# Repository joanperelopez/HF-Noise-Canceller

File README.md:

# HF Noise Canceller for ham radio

This project was born out of necessity for my day-to-day activities as a ham radio operator. The QRM is becoming more intense every day, with current levels reaching S9, so I needed to find a way to reduce it.  

All the noise cancellers I know are based on the same principle: the use of an auxiliary antenna that picks up the noise, which is then phase-inverted, amplified, and mixed with the signal-plus-noise coming from the main antenna. By properly adjusting the amplitude and phase in the noise amplifier, part of that noise can be canceled out.

#### Note: This device is still in the design phase and the circuit has not yet been tested.

The original design is based on an article for building a noise canceller by colleague EA1KO, which in turn is very similar to a commercial one. I have applied some modifications that presumably could improve its performance, such as:

1. The incorporation of signal relays instead of extending the RF cables to the switches. This ensures that the wiring is entirely DC, with no RF signals. Due to these relays, the wiring is simplified.

2. The addition of a 1.2 MHz high-pass filter at the input of the auxiliary antenna. The use of this filter can be selected or bypassed via a switch.

3. PTT input from the transceiver to switch the canceller to transmit mode (in this mode, the power relay creates a bypass between the main antenna and the transceiver). The automatic switching when RF is detected is only as a safety measure.

4. LA1, LA2, and LA3 are 12V bulbs used to protect sensitive circuits from RF power when the equipment is in transmission mode.

5. The addition of shielding in the first stage of noise amplification, to prevent noise that does not come from the auxiliary antenna.

6. A careful design of the ground connections, their points of connection to the main ground, and the power supply inputs.

7. Adjustment of the delay time from when the PTT is released until the device returns to reception mode.

8. A single power relay for antenna switching.

_Top view of the 3D model._

_Bottom view of the 3D model._

### Additional information for assembly:  

1. Once the SMD and THT components are mounted on the PCB, the jumpers marked from JP1 to JP6 need to be short-circuited. These jumpers are a very effective method to determine where the ground connections and power supply positives are linked across the entire PCB.

2. A 50-ohm coaxial cable needs to be placed to connect TP15 and TP13 with TP14 and TP12, respectively. I have preferred this connection to be made using an external cable rather than a copper trace to avoid possible interference (EMI). This cable is marked in the PCB silkscreen.

3. All cables going to connectors and switches must be connected to the corresponding TPn, according to the schematic.

_PCB Top side._

_PCB Bottom side._

### RF Transformers
All the transformers used in the design are identical. The ferrite cores employed are BN-73-302 or similar, with a permeability of around 2500.

To make each transformer, two wires of different colors (to easily identify their ends) need to be twisted together. With this twisted wire, five turns must be wound around the toroid, keeping in mind that each time the wire passes through a hole in the toroid, it counts as one turn. 

The figure shows how to number the terminals to correctly install the transformers on the printed circuit board.

_Detail of each transformer and their terminal numbers._

_3D model top view._

_3D model front view. You must include knobs to adjust the potentiometers._

_3D model rear view._

_Printed 3D prototype. Ready to be used._ 

_Printed 3D prototype. Ready to be used._ 

_Printed 3D potentiometer extender. Ready to be used._ 

### Errors found
1. Q2 and Q5 have the E and the B footprints interchanged.
2. The diodes 1N4148 have the footprint to small.

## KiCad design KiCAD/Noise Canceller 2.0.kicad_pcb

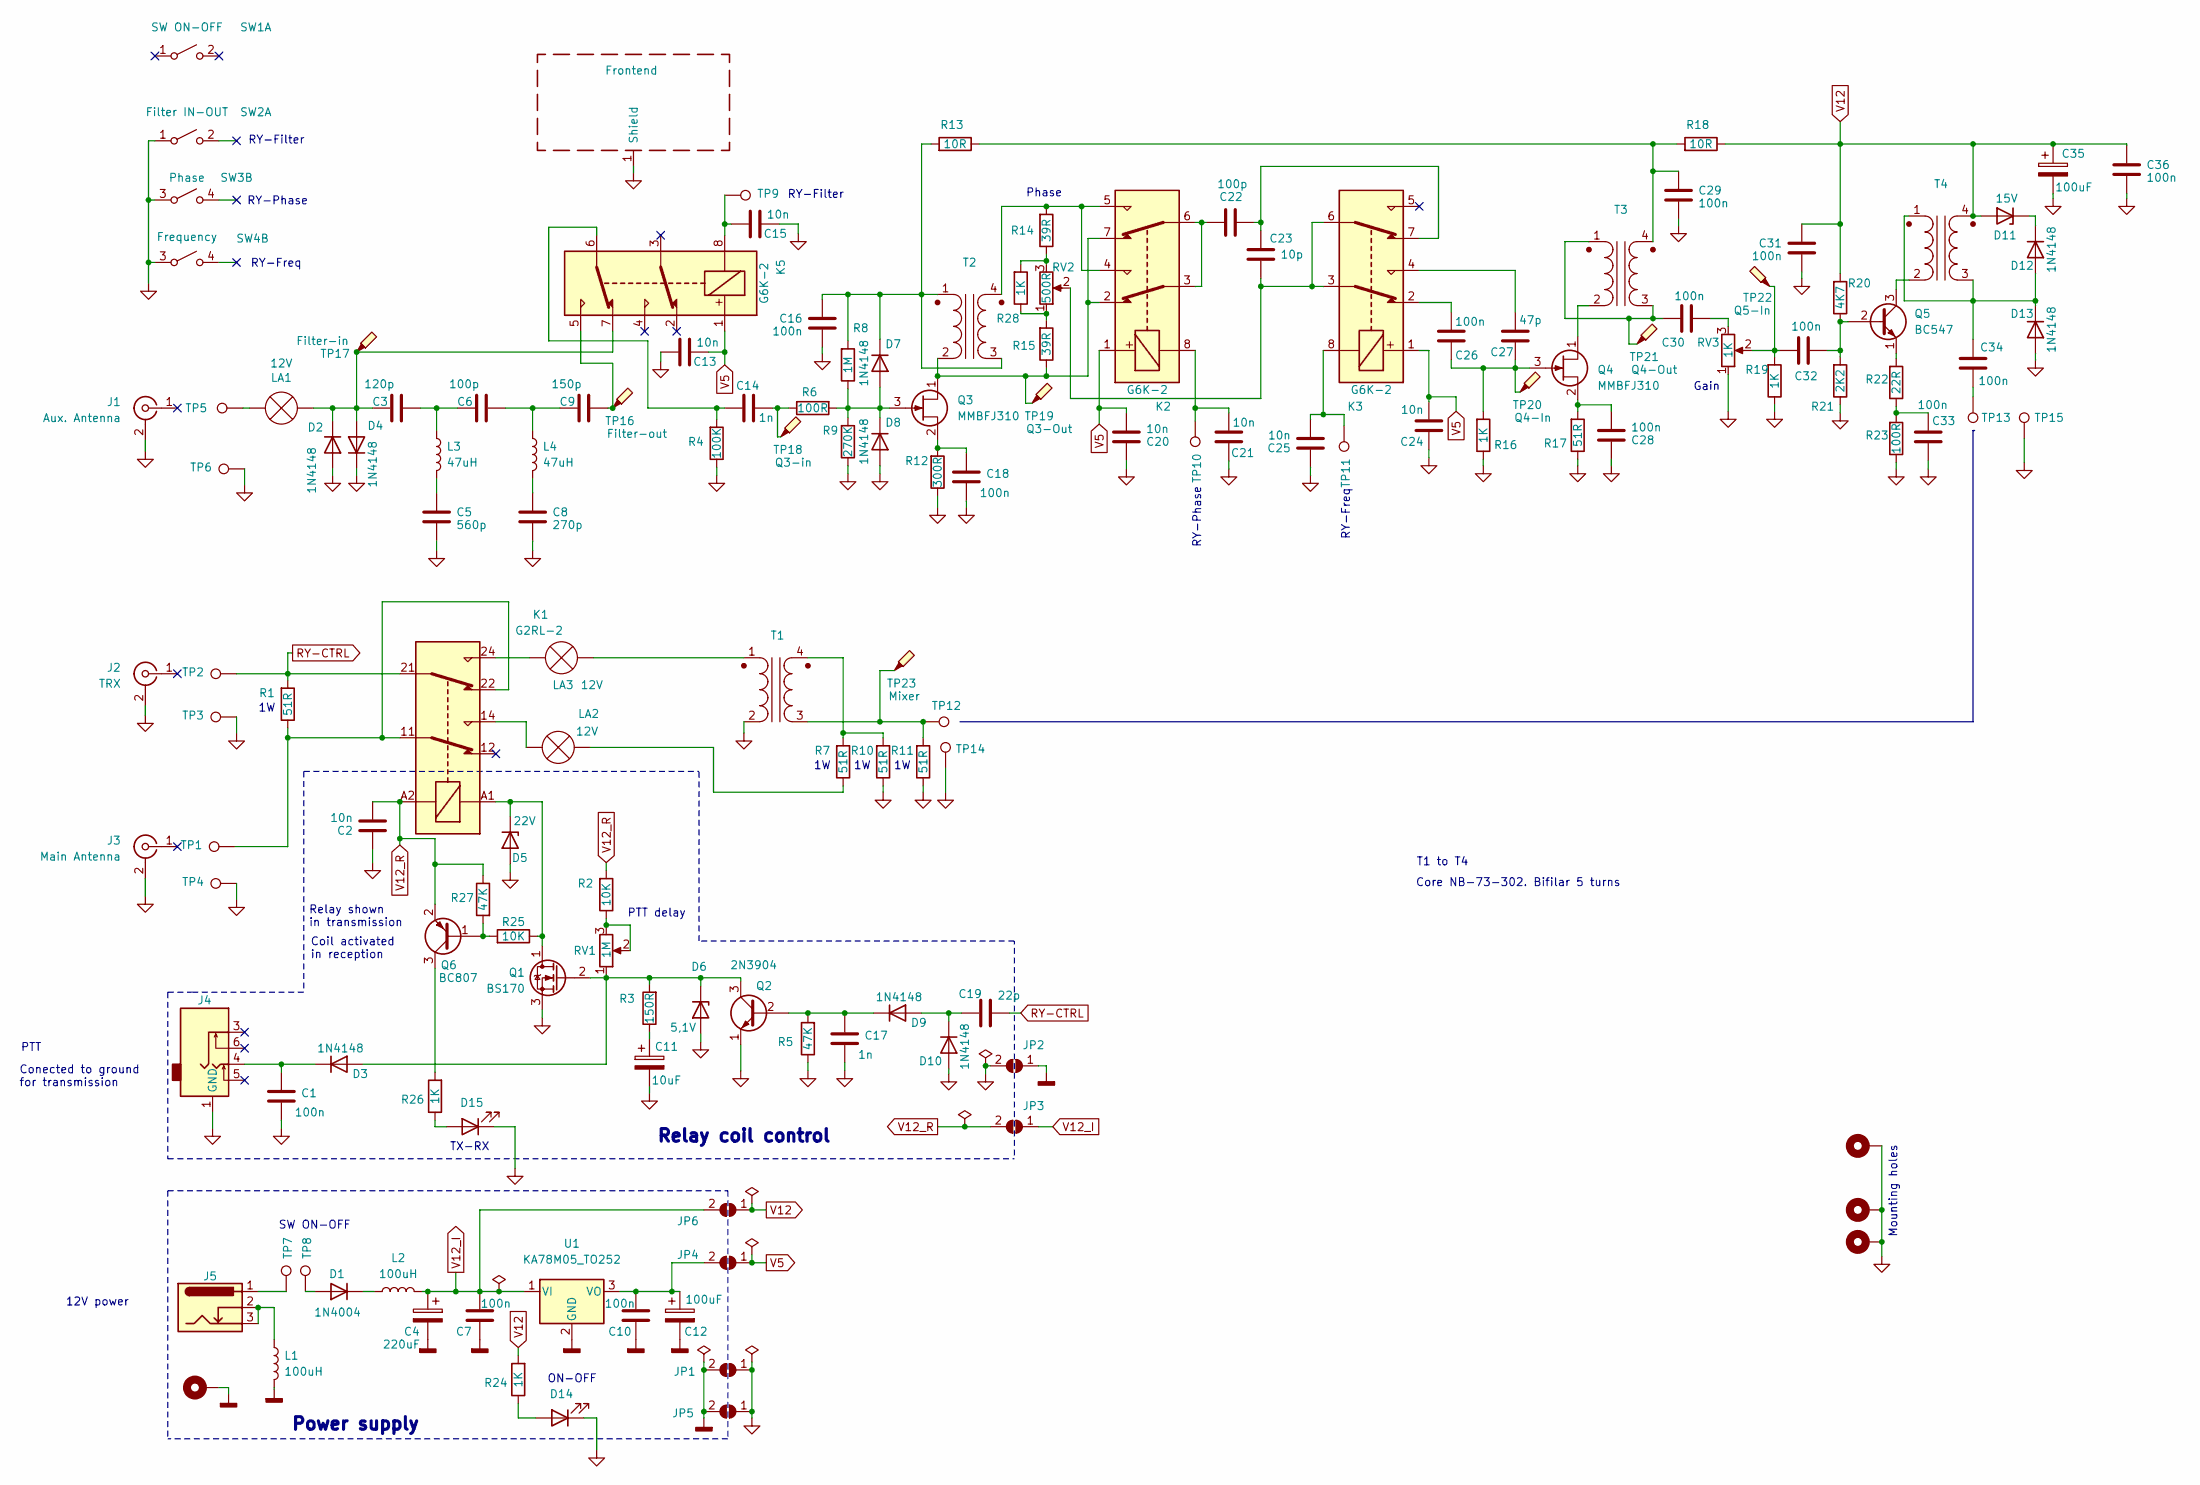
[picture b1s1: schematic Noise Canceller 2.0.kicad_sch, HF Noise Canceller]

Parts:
C1, C7, C10, C16, C18, C26, C28, C29, C30, C31, C32, C33, C34, C36: 100n; C_0805_2012Metric
C2, C13, C15, C20, C21, C24, C25: 10n; C_0805_2012Metric
C3: 120p; C_0805_2012Metric
C4: 220uF; C_Elec_8x10.2
C5: 560p; C_0805_2012Metric
C6, C22: 100p; C_0805_2012Metric
C8: 270p; C_0805_2012Metric
C9: 150p; C_0805_2012Metric
C11: 10uF; CP_Elec_5x5.4
C12, C35: 100uF; C_Elec_8x10.2
C14, C17: 1n; C_0805_2012Metric
C19: 22p; C_0805_2012Metric
C23: 10p; C_0805_2012Metric
C27: 47p; C_0805_2012Metric
D1: 1N4004; D_5W_P5.08mm_Vertical_KathodeUp
D2, D3, D4, D7, D8, D9, D10, D12, D13: 1N4148; D_0805_2012Metric
D5: 22V; D_DO-35_SOD27_P7.62mm_Horizontal
D6: 5,1V; D_DO-35_SOD27_P7.62mm_Horizontal
D11: 15V; D_DO-35_SOD27_P7.62mm_Horizontal
D14, D15: LED; LED_D3.0mm_Horizontal_O1.27mm_Z10.0mm
H1, H2, H3, H4: MountingHole_Pad; MountingHole_3.2mm_M3_Pad_TopBottom
J1: Aux. Antenna
J2: TRX
J3: Main Antenna
J4: AudioJack4_PERE; AUDIO-JACK4
J5: Barrel_Jack_Switch_Pin3Ring; BarrelJack_GCT_DCJ200-10-A_Horizontal
J6: Frontend; Shielding 20x25
JP1, JP2, JP3, JP4, JP5, JP6: SolderJumper_2_Open; SolderJumper-2_P1.3mm_Open_RoundedPad1.0x1.5mm
K1: G2RL-2; Relay_DPDT_Omron_G2RL-2
K2, K3, K5: G6K-2; Relay_DPDT_Omron_G6K-2F-Y
L1, L2: 100uH; L_1206_3216Metric
L3, L4: 47uH; L_1206_3216Metric
LA1, LA2, LA3: 12V; LED_D3.0mm_FlatTop
Q1: BS170; TO-92_Inline
Q2: 2N3904; SOT-23
Q3, Q4: MMBFJ310; SOT-23
Q5: BC547; SOT-23
Q6: BC807; SOT-23
R1, R7, R10, R11: 51R; R_2512_6332Metric
R2, R25: 10K; R_0805_2012Metric
R3: 150R; R_0805_2012Metric
R4: 100K; R_0805_2012Metric
R5, R27: 47K; R_0805_2012Metric
R6, R23: 100R; R_0805_2012Metric
R8: 1M; R_0805_2012Metric
R9: 270K; R_0805_2012Metric
R12: 300R; R_0805_2012Metric
R13, R18: 10R; R_0805_2012Metric
R14, R15: 39R; R_0805_2012Metric
R16, R19, R24, R26, R28: 1K; R_0805_2012Metric
R17: 51R; R_0805_2012Metric
R20: 4K7; R_0805_2012Metric
R21: 2K2; R_0805_2012Metric
R22: 22R; R_0805_2012Metric
RV1: 1M; Potentiometer_Piher_PT-6-V_Vertical_Hole
RV2: 500R; Potentiometer_Alps_RK163_Single_Horizontal
RV3: 1K; Potentiometer_Alps_RK163_Single_Horizontal
SW1: SW ON-OFF
SW2: Filter IN-OUT
SW3: Phase
SW4: Frequency
T1, T2, T3, T4: BN-73-202
TP1, TP2, TP3, TP4, TP5, TP6, TP7, TP8, TP9, TP10, TP11, TP12, TP13, TP14, TP15: TestPoint; MountingHole_2.2mm_M2_DIN965_Pad_TopBottom
TP16: Filter-out; TestPoint_Pad_D1.5mm
TP17: Filter-in; TestPoint_Pad_D1.5mm
TP18: Q3-in; TestPoint_Pad_D1.5mm
TP19: Q3-Out; TestPoint_Pad_D1.5mm
TP20: Q4-In; TestPoint_Pad_D1.5mm
TP21: Q4-Out; TestPoint_Pad_D1.5mm
TP22: Q5-In; TestPoint_Pad_D1.5mm
TP23: Mixer; TestPoint_Pad_D1.5mm
U1: KA78M05_TO252; TO-252

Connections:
GND: C5.2, C8.2, C13.2, C15.1, C16.2, C18.2, C20.1, C21.1, C24.1, C25.1, C28.1, C29.2, C31.2, C33.1, C35.2, C36.2, D2.2 (A), D4.1 (K), D8.2 (A), D13.2 (A), D14.1 (K), D15.1 (K), H1.1, H3.1, H4.1, J1.2 (Ext), J2.2 (Ext), J3.2 (Ext), J6.1 (Shield), JP1.1 (A), JP5.1 (A), R4.1, R9.1, R10.1, R11.1, R12.1, R16.1, R17.1, R19.1, R21.1, R23.1, RV3.1, SW2.1 (A), SW3.3 (A), SW4.3 (A), T1.2 (AB), TP3.1, TP4.1, TP6.1, TP14.1, TP15.1
GND1: C1.2, C2.1, C11.2, C17.2, D5.2 (A), D6.2 (A), D10.2 (A), J4.1 (GND), JP2.2 (B), Q1.3 (S), Q2.1 (E), R5.1
GNDD: C4.2, C7.1, C10.1, C12.2, H2.1, JP1.2 (B), JP2.1 (A), JP5.2 (B), L1.2, U1.2 (GND)
unnamed: C3.2, C6.1, L3.1
unnamed: C5.1, L3.2
unnamed: C6.2, C9.1, L4.1
unnamed: C8.1, L4.2
unnamed: C9.2, K5.5, TP16.1
unnamed: C11.1, R3.1
unnamed: C14.1, K5.6, R4.2
unnamed: C14.2, R6.1, TP18.1
unnamed: C15.2, K5.8, TP9.1
unnamed: C21.2, K2.8, TP10.1
unnamed: C22.1, K2.3, K2.6
unnamed: C22.2, C23.1, K3.7
unnamed: C23.2, K3.3, K3.6, RV2.2
unnamed: C25.2, K3.8, TP11.1
unnamed: C26.2, K3.2
unnamed: C27.2, K3.4
unnamed: C30.1, RV3.3
unnamed: C32.2, R19.2, RV3.2, TP22.1
unnamed: C33.2, R22.1, R23.2
unnamed: C34.2, TP13.1
unnamed: D1.2 (A), TP8.1
unnamed: D1.1 (K), L2.1
unnamed: C3.1, D2.1 (K), D4.2 (A), K5.7, LA1.1 (-), TP17.1
unnamed: D3.2 (A), D6.1 (K), Q1.2 (G), Q2.3 (C), R3.2, RV1.1
unnamed: C1.1, D3.1 (K), J4.4
unnamed: D5.1 (K), K1.A1, Q1.1 (D), R25.1
unnamed: D7.2 (A), D8.1 (K), Q3.3 (G), R6.2, R8.1, R9.2
unnamed: C16.1, D7.1 (K), R8.2, R13.2, T2.1 (AA), T2.3 (SA)
unnamed: C17.1, D9.1 (K), Q2.2 (B), R5.2
unnamed: C19.1, D9.2 (A), D10.1 (K)
unnamed: D11.1 (K), D12.1 (K)
unnamed: C34.1, D12.2 (A), D13.1 (K), T4.1 (AA), T4.3 (SA)
unnamed: D14.2 (A), R24.1
unnamed: D15.2 (A), R26.1
unnamed: J5.1, TP7.1
unnamed: J5.2, J5.3, L1.1
unnamed: C10.2, C12.1, JP4.2 (B), U1.3 (VO)
unnamed: K1.11, K1.22, R1.1, TP1.1
unnamed: LA1.2 (+), TP5.1
unnamed: K1.14, LA2.2 (+)
unnamed: LA2.1 (-), R7.1
unnamed: K1.24, LA3.2 (+)
unnamed: LA3.1 (-), T1.1 (AA)
unnamed: K2.2, K2.7, Q3.1 (D), R15.1, T2.2 (AB), TP19.1
unnamed: C18.1, Q3.2 (S), R12.2
unnamed: Q4.1 (D), T3.2 (AB)
unnamed: C26.1, C27.1, Q4.3 (G), R16.2, TP20.1
unnamed: C28.2, Q4.2 (S), R17.2
unnamed: C32.1, Q5.2 (B), R20.1, R21.2
unnamed: Q5.3 (C), T4.2 (AB)
unnamed: Q5.1 (E), R22.2
unnamed: Q6.1 (B), R25.2, R27.2
unnamed: Q6.3 (C), R26.2
unnamed: R2.1, RV1.2, RV1.3
unnamed: R14.1, R28.2, RV2.3
unnamed: R15.2, R28.1, RV2.1
unnamed: R11.2, T1.3 (SA), TP12.1, TP23.1
unnamed: R7.2, R10.2, T1.4 (SB)
unnamed: K2.4, K2.5, R14.2, T2.4 (SB)
unnamed: C30.2, T3.1 (AA), T3.3 (SA), TP21.1
unnamed: C29.1, R13.1, R18.2, T3.4 (SB)
RY-CTRL: C19.2, K1.21, R1.2, TP2.1
V5: C13.1, C20.2, C24.2, JP4.1 (A), K2.1, K3.1, K5.1
V12: C31.1, C35.1, C36.1, D11.2 (A), JP6.1 (A), R18.1, R20.2, R24.2, T4.4 (SB)
V12_I: C4.1, C7.2, JP3.1 (A), JP6.2 (B), L2.2, U1.1 (VI)
V12_R: C2.2, JP3.2 (B), K1.A2, Q6.2 (E), R2.2, R27.1

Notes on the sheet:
Conected to ground for transmission
Relay shown in transmission
PTT
Phase
RY-Phase
T1 to T4
TX-RX
Gain
RY-Freq
Power supply
ON-OFF
Mounting holes
PTT delay
SW ON-OFF
Relay coil control
RY-Filter
Coil activated in reception
Core NB-73-302. Bifilar 5 turns
12V power

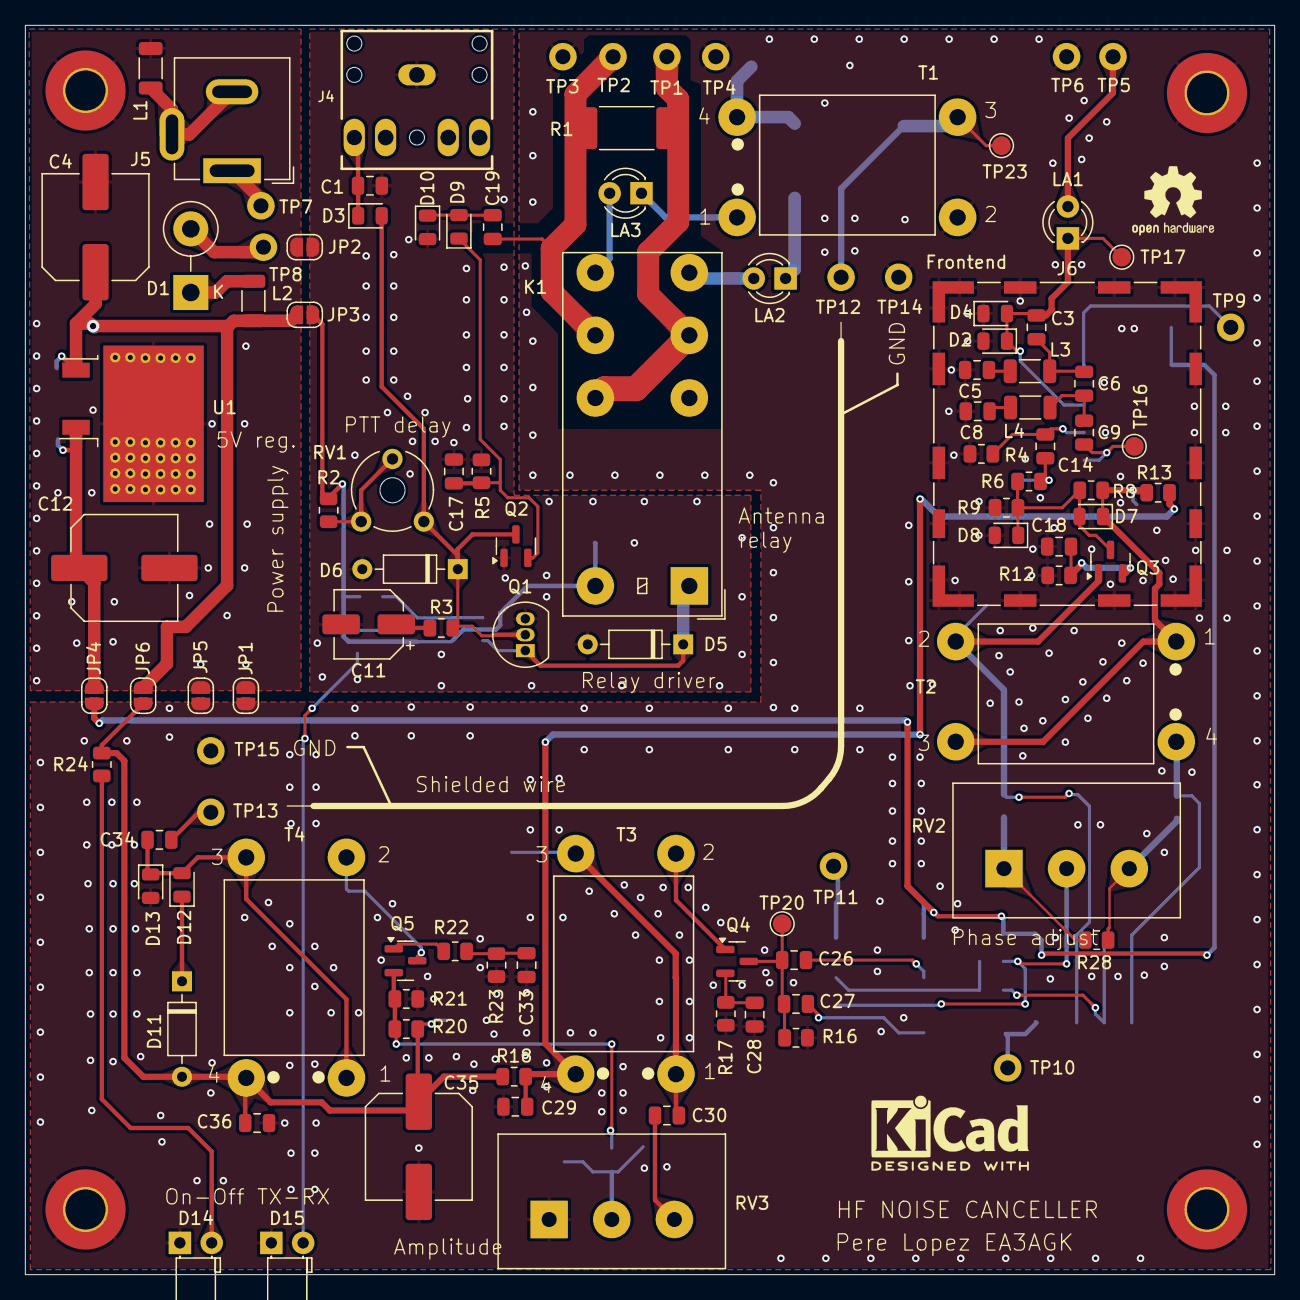
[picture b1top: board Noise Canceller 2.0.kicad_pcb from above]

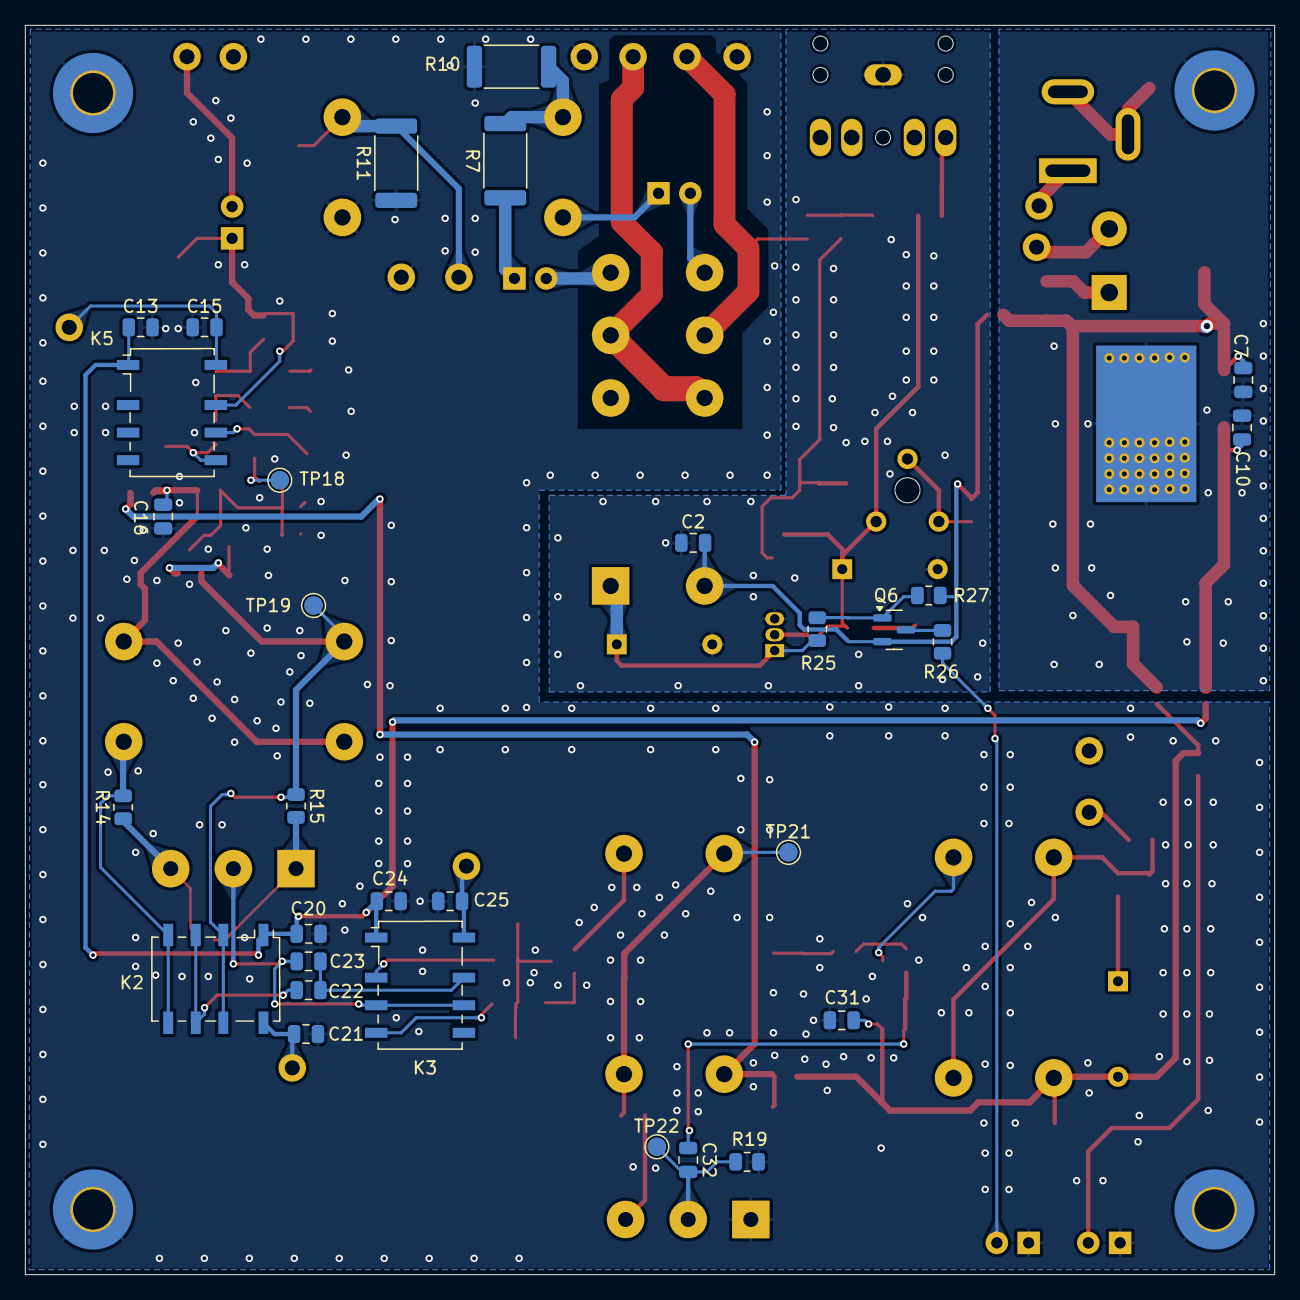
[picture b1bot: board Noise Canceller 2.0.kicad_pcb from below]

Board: 2 copper layers, 99.7 x 99.7 mm, 140 parts (31 on the bottom side), 69 nets.

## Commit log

2025-04-17 Create KiCAD
2025-04-17 Create rd
